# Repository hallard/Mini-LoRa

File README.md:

Mini Lora Node, Arduino Mini LoraWAN sensor
===========================================

At the beginning this PCB has been created to help wiring between Arduino Mini and RFM95 Lora module and to be able to put the whole thing powered by various Batteries type (AA, 18650, A, ...).

Then I decided to add some funky stuff like:

**new in V1.2**

- Footprint for Ultra Low Power controller TPL5110
- R9 1206 or PTH Footprint to easily change resistor and thus delay between wake
- renamed silk pin to function instead of arduino name
- Optional Tactile Switch to wake from TPL5110

**all version**

- Easy to build and solder, 0805 or PTH components
- I2C connector (or grove) to be able to add internal/external sensors such as BME280, SI7021 or HTU21D
- Footprint for Lora RFM95
- Footprint for a Microchip 24AA02E64T EUID 
- RBG Led
- Optional Tactile Switch
- Various Battery Connector and type AA/A/18650/CR123
- Two A4/A5 pins position so you can use different Mini Clone (see BOM)

**On version 1.1, I2C A4/A5 (the ones bottom right) are not connected**, thanks to tkerby who detected this point on [issue #1](https://github.com/hallard/Mini-LoRa/issues/1).
This is now fixed on version 1.1a. Pcbs.io PCB have been updated.

Detailed Description
====================

No specific documentation for now, it's just a kind of wiring helper as follow

```
 Arduino Mini   RFM9x Module
 A0          <----> RST
 MISO  (D12) <----> MISO
 MOSI  (D11) <----> MOSI
 SCK   (D13) <----> CLK
 SS    (D10) <----> SEL (Chip Select)
 D2          <----> DIO0
 D7          <----> DIO1
 D8          <----> DIO2

 Arduino Mini    Shield PCB
 D3          <----> Push Button (Has Pull Down)
 D9          <----> Led Red
 D6          <----> Led Green
 D5          <----> Led Blue
 A1          <----> DONE of TPL5110 (to indicate we done)
 A2          <----> DRVN of TPL5110 (pulse out to wake CPU)
 SDA (A4)    <----> I2C SCL Connector
 SCL (A5)    <----> I2C SDA Connector
```

R9 determine Wake Time interval from TPL5110 as follow 
  - 170K 2 hours
  - 120K ~1 hour
  - 100K ~35 min
  - 47K ~6 min

please read TPL5110 [datasheet](http://www.ti.com/lit/ds/symlink/tpl5110.pdf) for more information or Adafruit TPL5110 Learning [page](https://learn.adafruit.com/adafruit-tpl5110-power-timer-breakout/)

Installation
============

If you're using Battery clip connector, please isolate the A4/A5 and FTDI (V1.0 only) pads from clip because it will do shorts and prevent I2C to work.

I'm Using the [LMIC stack](https://github.com/matthijskooijman/arduino-lmic) as his with custom sketch, this one is under NDA for Ultra Low Power, So I can't provide it but you can use the one in example of LMIC.

You may need to disable debug of LMIC stack if missing.

I'm also changing the Bootloader to use optiboot and win 1.5K of flash code and setup the Brown Out Detect to 1.8V to be able to works under 2.7V. Please see this [Pro-Mini-ICSP-FTDI](https://github.com/hallard/Pro-Mini-ICSP-FTDI) repo if you need to flash your Arduino Pro Mini with this bootloader. You'll see in [bootloader](https://github.com/hallard/Pro-Mini-ICSP-FTDI/tree/master/bootloaders) folder, I've compiled some for various Speed and for 8MHz and 16MHz Crystal (I use the 250KBPS one, it's fast and reliable).

I've also created custom board definition for Arduino IDE so if using my bootloader, you'll have the board clock and serial speed selection in Arduino IDE, it located [here](https://github.com/ch2i/ch2i-arduino-boards)

Schematic
=========

Boards 
======

**Top & bottom side V1.2**

**Top & bottom side Grove V1.1**

~~You can order PCBs of this board at [PCBs.io][3]~~

- ~~[V1.2](https://www.PCBs.io/share/r1a3J) Classic I2C connector~~
- ~~[V1.1a](https://www.PCBs.io/share/8AGb2) Classic I2C connector~~
- ~~[V1.1a](https://www.PCBs.io/share/zjKdY) Grove I2C connector~~
- ~~[V1.0](https://www.PCBs.io/share/r3LdE)~~

 ~~PCBs.io give me some reward when you order my designed boards from their site. This is pretty good, because I can use these rewards to create and design new boards and order boards for a discounted price, so if you don't care about PCB manufacturer please use PCBs.io.~~

Looks like PCBs.io is gone, I do not have any rewards from PCBs.io since August 2020 and my free order placed after are still not received, so my guess they are not on business anymore.

So you can order the board on [oshpark](https://oshpark.com). 

- [V1.2](https://oshpark.com/shared_projects/xBynTfXX) Classic I2C connector
- [V1.1a](https://oshpark.com/shared_projects/TSE77q5q) Groove I2C connector

It's a pitty after several discuss with OSHPark that I can't have any rewards for each people ordering my boards, this would allow me to order free PCB for shared projects and create new ones. For information my shared boards generated a total of **$285 162.00** orders at PCBs.io in 4 years, not bad at all :-)

Hoping one day OSHparks will thanks me giving them this market. 

Assembled boards with sensors
=============================

Sensors values en Cayenne

Bill Of Material
================

Nothing fancy, all components are 0805 and/or PTH and can be ordered almost anywhere (digikey, mouser, radiospare, ...). 
use only what you need dependings on what you want to do. 

Octopart [BOM file](https://octopart.com/bom-tool/MsqCYjTr)

Example of option parts, and other source
- Arduino Pro Mini (just take care your board has A4/A5 at the correct place, some clone are not)
    - [Geekcreit](https://www.banggood.com/Pro-Mini-ATMEGA328P-5V16M-Improved-Version-Module-For-Arduino-p-985618.html) 5V 16MHz (power it with 3.3V and/or remove regulator)
    - [ebay](http://www.ebay.com/itm/201562503063) 3V3 8MHz
- [RFM95](https://www.digikey.com/product-detail/en/rf-solutions/RFM95W-868S2/RFM95W-868S2-ND/5051755) (check Frequency)
- Common Anode RGB Led, search `diffused 5MM RGB LED common anode` on ebay
- Battery Connector format
    - Holder [AA](https://www.digikey.com/product-detail/en/mpd-memory-protection-devices/BCAAPC/BCAAPC-ND/232723)
    - Clip [AA](https://www.digikey.com/product-detail/en/mpd-memory-protection-devices/BK-92/BK-92-ND/2079904)
    - Clip [A/18650](https://www.digikey.com/product-detail/en/keystone-electronics/54/36-54-ND/2254090) 
    - PTH [CR123](https://www.digikey.com/product-detail/en/mpd-memory-protection-devices/BH123A/BH123A-ND/2817712)
- Batteries
    - 3.0V Lithium [CR123](https://www.digikey.com/product-detail/en/panasonic-bsg/CR-123PE-BN/P703-ND/7064720)
    - 3.6V Lithium Thionyle Chloride [2600mAh](http://fr.rs-online.com/web/p/piles-aa/2019438/)
    - 3.6V Lithium Thionyle Chloride [3600mAh](http://fr.rs-online.com/web/p/piles-aa/778-1087/)

License
=======

This work is licensed under a [Creative Commons Attribution-NonCommercial-ShareAlike 4.0 International License](https://creativecommons.org/licenses/by-nc-sa/4.0/)    
If you want to do commercial stuff with this project, please contact [CH2i company](https://www.ch2i.eu/en#support) so we can organize an simple agreement.

Misc
====

See TTN dedicated [post](https://www.thethingsnetwork.org/forum/t/8059) and news and other projects on my [blog][1] 
 
[1]: https://hallard.me
[3]: https://www.PCBs.io

[20]: http://www.seeedstudio.com/depot/index.php?main_page=opl_info&opl_id=4
[21]: http://www.ebay.com/itm/170578495165
[22]: http://www.ebay.com/itm/351690376555
[23]: http://www.ebay.com/itm/351738196013
[24]: http://www.ebay.com/itm/371534934746
[25]: https://www.adafruit.com/products/1979
[26]: https://www.sparkfun.com/products/11114

[27]: http://www.ebay.com/itm/121929386506?var=420920026758
[28]: http://www.ebay.com/itm/371348168950
[29]: http://www.ebay.com/itm/351588181858

[40]: http://www.ebay.com/itm/262500056078
[41]: http://www.aliexpress.com/item/Free-Shipping-Good-Quality-ABS-Material-Transparent-Cover-IP66-Waterproof-Electrical-Switch-Box-125-125-75mm/32522255056.html
[42]: http://www.aliexpress.com/item/Temperature-and-humidity-Protective-sleeve-Accessories-PCB-for-SHT20-SHT21-SHT25/32695663191.html?spm=2114.13010208.99999999.264.dgLxek
[43]: http://www.ebay.com/itm/401000227934
[44]: http://www.ebay.com/itm/182181715511?var=483966356069
[46]: http://www.ebay.com/itm/391462862706
[47]: http://www.ebay.com/itm/232153789354?var=531358445664
[48]: http://www.ebay.com/itm/301856945402

[50]: https://octopart.com/bom-tool/MsqCYjTr

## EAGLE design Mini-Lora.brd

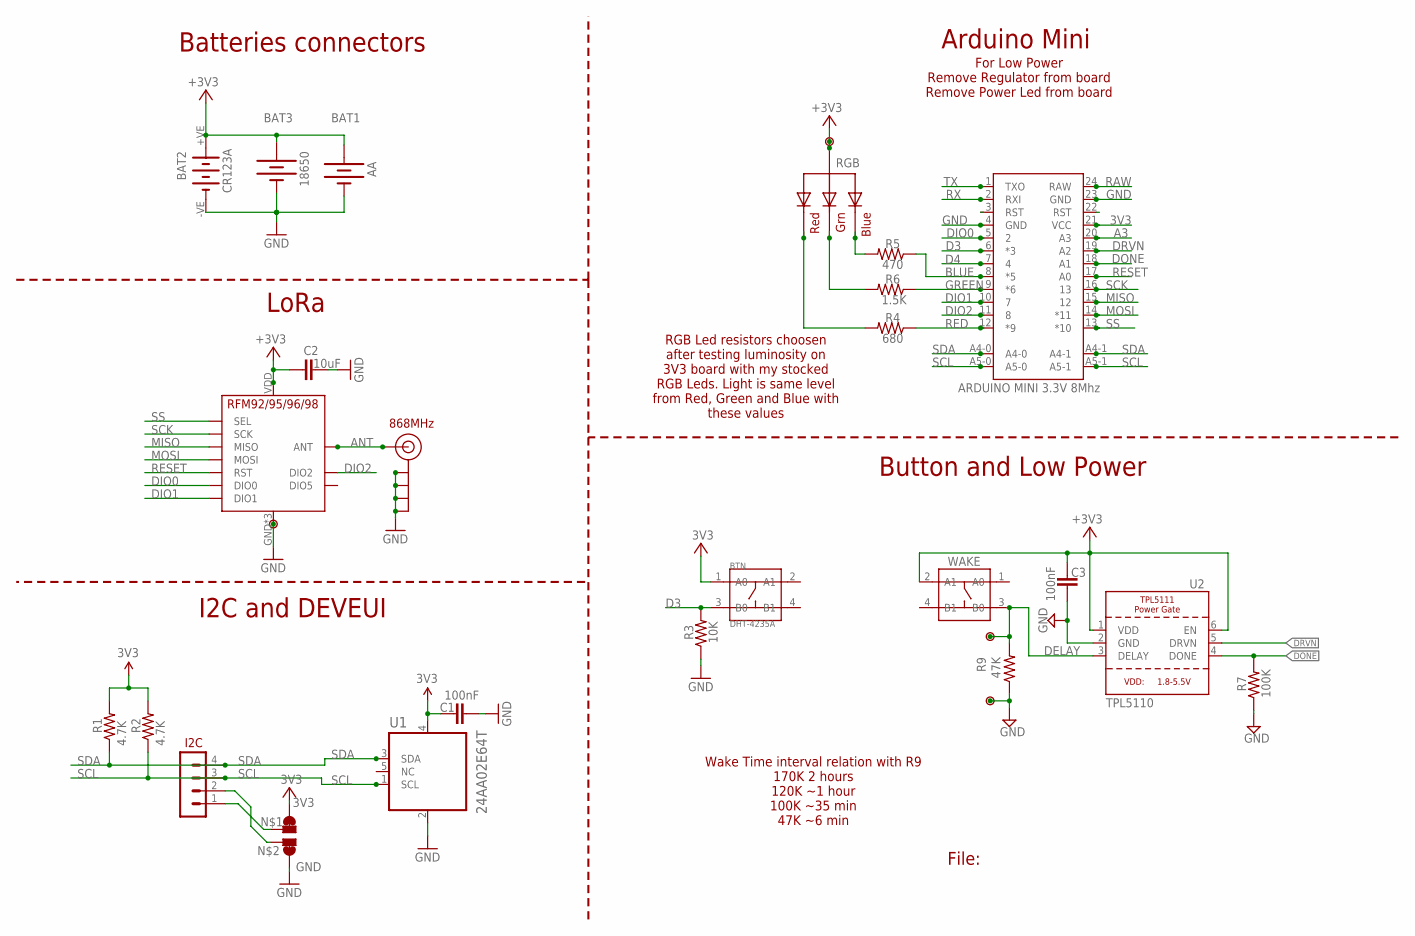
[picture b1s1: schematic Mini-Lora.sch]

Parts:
BAT1: AA; BATTERY-AA
BAT2: CR123A; KEYSTONE-2/3A
BAT3: 18650; BATTERY_18650-HOLDER
BTN: DHT-4235A; SW4-SMD-4.2X3.2X2.5MM
C1, C3: 100nF; 0805-CAP
C2: 10uF; 0805-CAP-LARGEPADS
I2C: CON_HEADER_1X04'NO_LOCK'; 1X04_NO_LOCK
J$2: ANTENNATINY; SMA_UFL_PAD_TINY
P1: GND; PAD
P2, P3, P4: PADNORMAL; PAD
R1, R2: 4.7K; 0805-RES
R3: 10K; 0805-RES
R4: 680; 0805-RES
R5: 470; 0805-RES
R6: 1.5K; 0805-RES
R7: 100K; 0805-RES
R9: 47K; 1206-RES
RGB: RGBLED; LED5MMRGB_ST
U1: 24AA02E64T; SOT95P270X145-5N
U2: TPL5110; SOT23-6
U$1: PAD-JUMPER-SWAPSWAP; PAD-JUMPER-SWAP
U$5: RFM95
U$6: ARDUINO MINI 3.3V 8Mhz; ARDUINO_PRO_MINI
WAKE: WAKE; SW4-SMD-4.2X3.2X2.5MM

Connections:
3V3: BAT1.PWR@1 (+), BAT2.+VE (+), BAT3.PWR@1 (+), BTN.1 (A0), C1.1, C2.2, C3.1, P4.1, R1.2, R2.2, RGB.2 (VCC), U1.4 (VCC), U2.1 (VDD), U2.6 (EN), U$1.4, U$1.44 (4), U$5.VDD (VCC), U$6.21 (VCC), WAKE.2 (A1)
A3: U$6.20 (A3)
ANT: J$2.ANT1 (SIGNAL), J$2.ANT2 (SIGNAL), J$2.ANT3 (SIGNAL), U$5.ANT
BLUE: R5.1, U$6.8 (*5)
D3: BTN.3 (B0), R3.2, U$6.6 (*3)
D4: U$6.7 (4)
DELAY: P2.1, R9.2, U2.3 (DELAY), WAKE.3 (B0)
DIO0: U$5.DIO0, U$6.5 (2)
DIO1: U$5.DIO1, U$6.10 (7)
DIO2: U$5.DIO2, U$6.11 (8)
DONE: R7.2, U2.4 (DONE), U$6.18 (A1)
DRVN: U2.5 (DRVN), U$6.19 (A2)
GND: BAT1.GND@1 (-), BAT2.-VE (-), BAT3.GND@1 (-), C1.2, C2.1, C3.2, J$2.GND1 (GND), J$2.GND2 (GND), J$2.GND3 (GND), J$2.GND4 (GND), P1.1, P3.1, R3.1, R7.1, R9.1, U1.2 (VSS), U2.2 (GND), U$1.1, U$1.11 (1), U$5.GND, U$5.GND1 (GND), U$5.GND2 (GND), U$6.4 (GND), U$6.23 (GND)
GREEN: R6.1, U$6.9 (*6)
LB: R5.2, RGB.4 (BLUE)
LG: R6.2, RGB.3 (GREEN)
LR: R4.2, RGB.1 (RED)
MISO: U$5.MISO, U$6.15 (12)
MOSI: U$5.MOSI, U$6.14 (*11)
unnamed: I2C.1, U$1.3
unnamed: I2C.2, U$1.2
RAW: U$6.24 (RAW)
RED: R4.1, U$6.12 (*9)
RESET: U$5.RST, U$6.17 (A0)
RST: U$6.22 (RST)
RX: U$6.2 (RXI)
SCK: U$5.SCK, U$6.16 (13)
SCL: I2C.3, R2.1, U1.1 (SCL), U$6.A5-0, U$6.A5-1
SDA: I2C.4, R1.1, U1.3 (SDA), U$6.A4-0, U$6.A4-1
SS: U$5.NSS (SEL), U$6.13 (*10)
TX: U$6.1 (TXO)

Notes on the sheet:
File:
868MHz
Wake Time interval relation with R9 170K 2 hours 120K ~1 hour 100K ~35 min 47K ~6 min
Button and Low Power
Arduino Mini
I2C and DEVEUI
LoRa
Batteries connectors
For Low Power Remove Regulator from board Remove Power Led from board
RGB Led resistors choosen after testing luminosity on 3V3 board with my stocked RGB Leds. Light is same level from Red, Green and Blue with these values

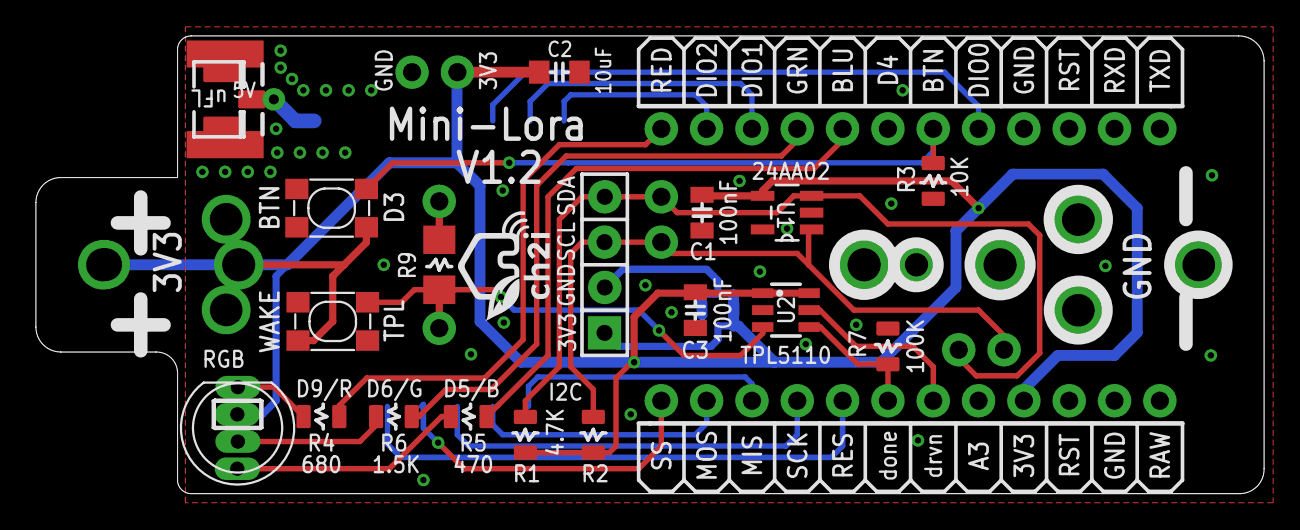
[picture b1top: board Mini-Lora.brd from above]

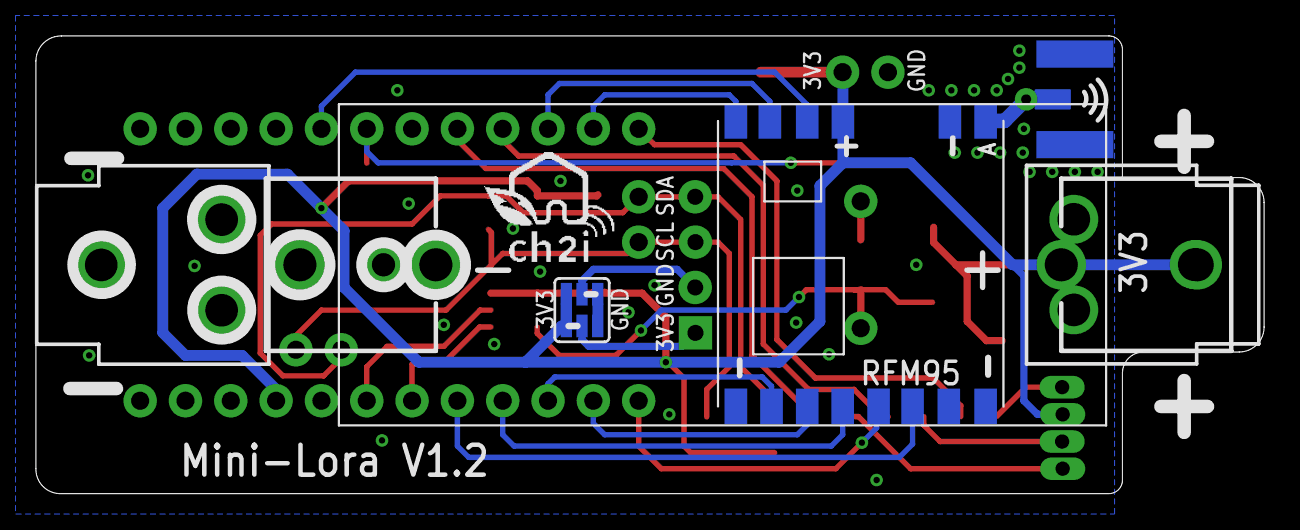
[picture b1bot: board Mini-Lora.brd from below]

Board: 2 copper layers, 68.8 x 25.7 mm, 30 parts (6 on the bottom side), 25 nets.

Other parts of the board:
U$2: LOGO_C2I_015
U$4: LOGO_CH2I_75MM

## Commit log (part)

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2017-07-06 :lollipop: Added .gitattributes
2017-07-06 Creation
2017-07-06 Link test
2017-07-06 test
2017-07-06 Moved to picture
2017-07-06 Corrected Links
2017-07-06 Added Bootloaders
2017-07-06 Added bootloader
2017-07-25 real pictures
2017-07-25 Moved to Pro-Mini-ICSP-FTDI repo
2017-07-25 Added new PCBs.io links
2017-09-18 Bump to V1.1a
2017-09-18 Updated BOM + V1.1a
2018-07-10 Bump to V1.2
2018-07-10 cosmetic
2018-07-10 Word mistake
2019-07-07 Added link toi boards definition
2021-01-12 Added OSHPark link
2021-01-12 set back V1.2

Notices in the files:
parts and their libraries:
edeca.net-v5: This is v1 and is licensed under the Creative Commons (Attribution-Non-Commercial-Share Alike 2.0 UK)
SparkFun-Aesthetics: Licensing: Creative Commons ShareAlike 4.0 International - https://creativecommons.org/licenses/by-sa/4.0
